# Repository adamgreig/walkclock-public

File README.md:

# walkclock

A clock that shows a map with a route that progresses day-by-day.

Display is a 64x64px LED matrix, driven by an STM32H743 on a WeAct dev board.

## Simulator

To run the simulator on a desktop:

```
cd simulator/
cargo run --release
```

The following keyboard buttons are mapped to the buttons on the hardware:

* Q/Backspace/Up: BACK
* W: QR
* E: DISPLAY
* A/Enter/Down: ENTER
* S/Left: LEFT
* D/Right: RIGHT

## Firmware

To program the firmware:

```
cd firmware/
cargo embed --release
```

Use `cargo embed --release rtt` to also attach an RTT session.

## Other Assets

* `mechanical/` contains design files for the 3d-printed holder and laser-cut
  acrylic diffuser
* `artwork/` contains the various maps and images, and a script to extract
  route pixel data from XCF files

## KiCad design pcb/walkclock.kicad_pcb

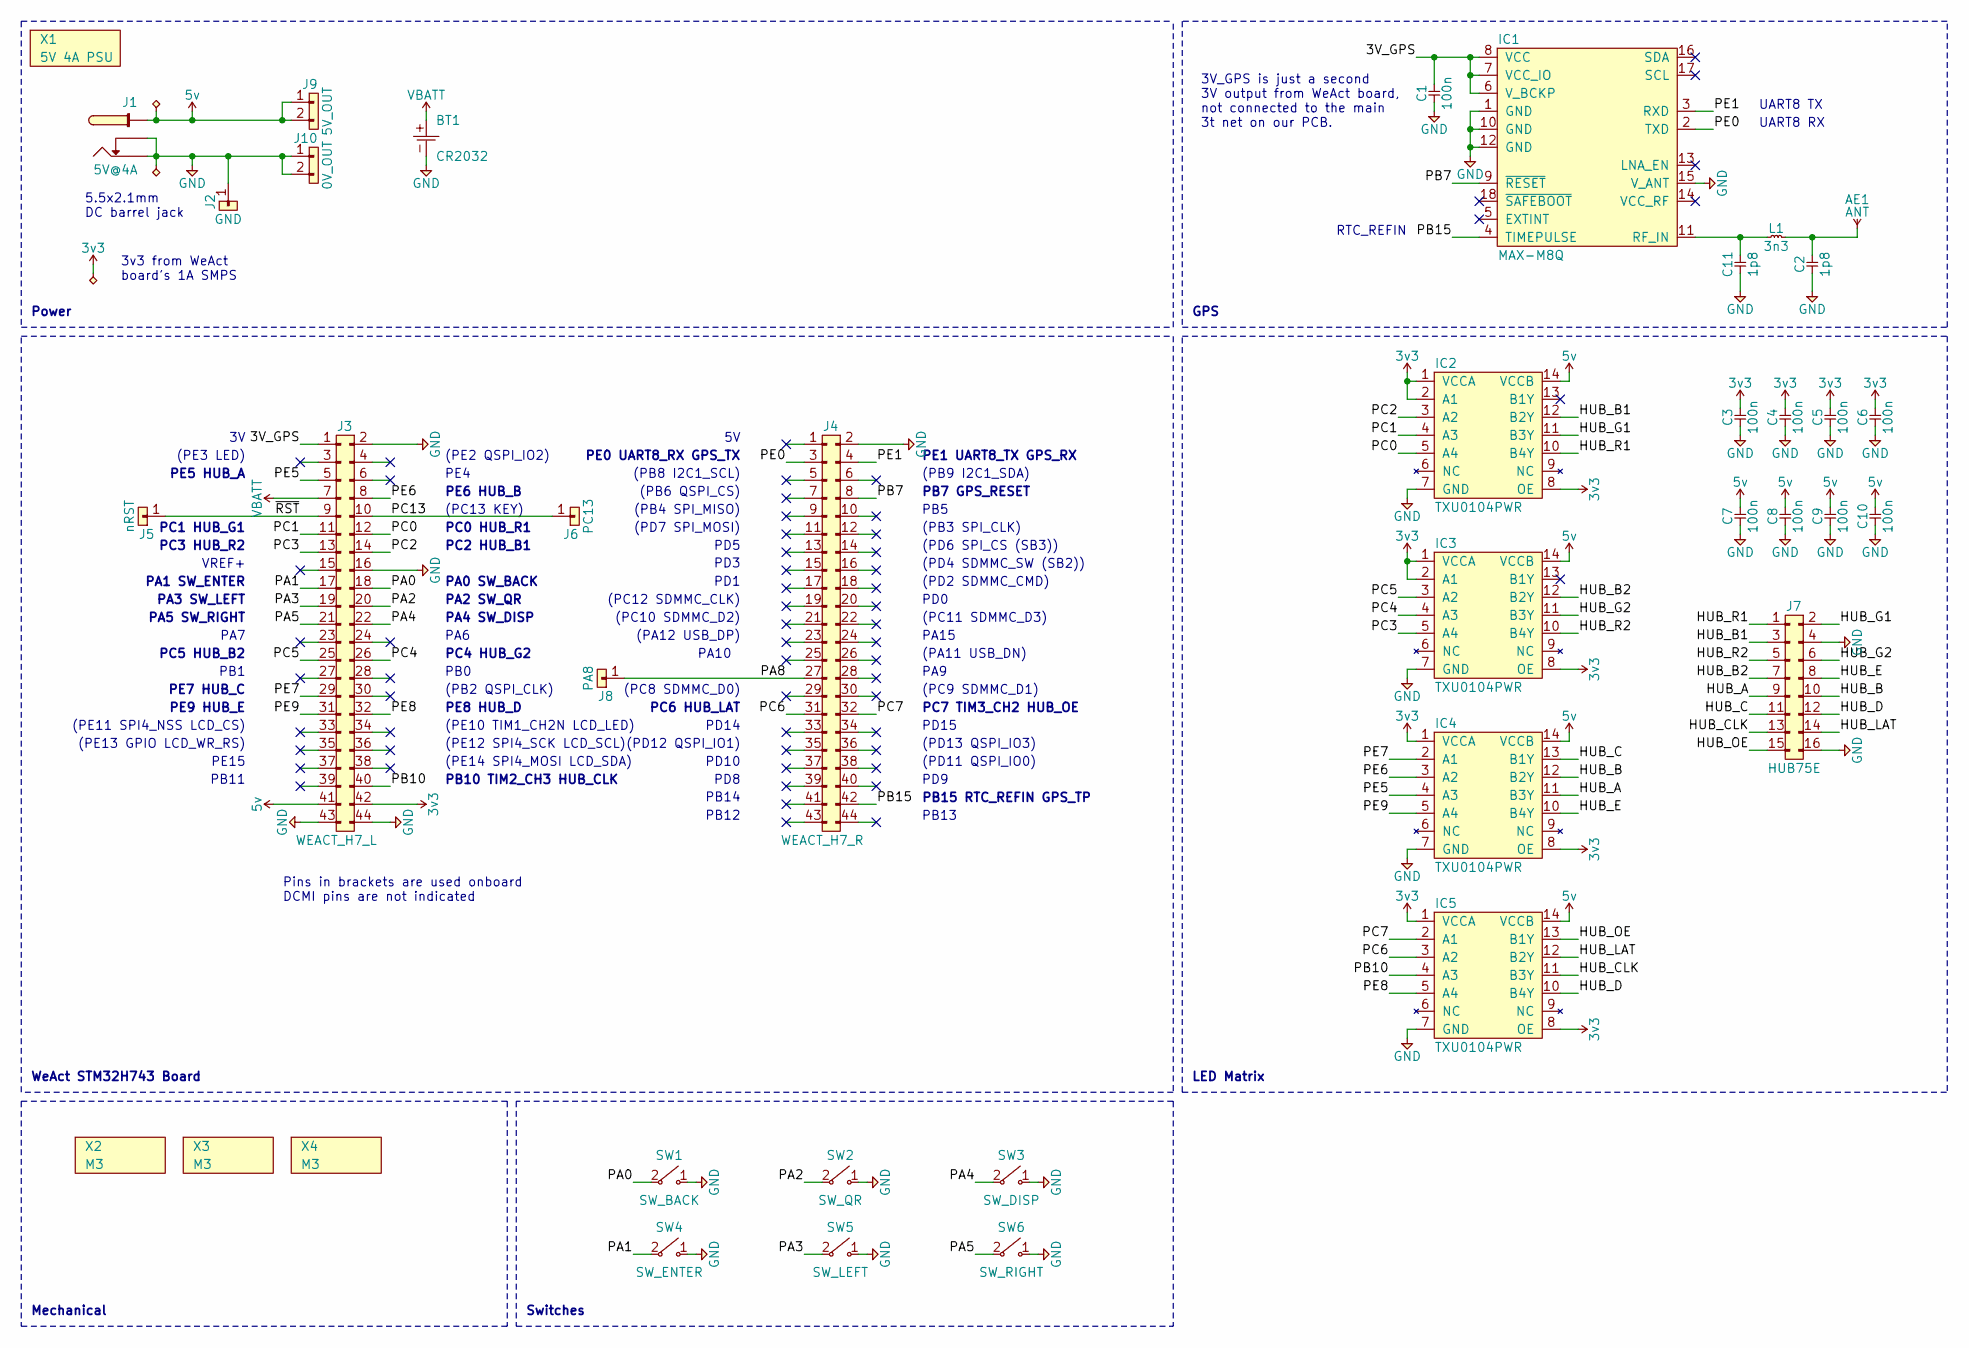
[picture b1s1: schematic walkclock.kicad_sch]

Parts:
AE1: ANT; NN01-103; Mouser 128-NN01-103
BT1: CR2032; KEYSTONE_103
C1, C3, C4, C5, C6, C7, C8, C9, C10: 100n; 0402; Mouser 963-TMK105BJ104KV8F
C2, C11: 1p8; 0402; Mouser 80-CBR04C189A5GAC
IC1: MAX-M8Q
IC2, IC3, IC4, IC5: TXU0104PWR; TSSOP-14; Mouser 595-TXU0104PWR
J1: 5V@4A; BARRELJACK
J2: GND; SIL-254P-01
J3: WEACT_H7_L; DIL-254P-44; Mouser 200-SSW12201FD
J4: WEACT_H7_R; DIL-254P-44; Mouser 200-SSW12201FD
J5: nRST; SIL-254P-01
J6: PC13; SIL-254P-01
J7: HUB75E; DIL-254P-16; Mouser 200-SSW10801FD
J8: PA8; SIL-254P-01
J9: 5V_OUT; SIL-254P-02
J10: 0V_OUT; SIL-254P-02
L1: 3n3; 0402; Mouser 81-LQW15AN3N3D10D
SW1: SW_BACK; SW_MOM_6X6; Mouser 179-TS046670BK260SMT
SW2: SW_QR; SW_MOM_6X6; Mouser 179-TS046670BK260SMT
SW3: SW_DISP; SW_MOM_6X6; Mouser 179-TS046670BK260SMT
SW4: SW_ENTER; SW_MOM_6X6; Mouser 179-TS046670BK260SMT
SW5: SW_LEFT; SW_MOM_6X6; Mouser 179-TS046670BK260SMT
SW6: SW_RIGHT; SW_MOM_6X6; Mouser 179-TS046670BK260SMT
X1: 5V 4A PSU; Mouser 418-TRE25050U11G02VI
X2, X3, X4: M3; M3_HOLE

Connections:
3v3: C3.2, C4.2, C5.2, C6.2, IC2.1 (VCCA), IC2.2 (A1), IC2.8 (OE), IC3.1 (VCCA), IC3.2 (A1), IC3.8 (OE), IC4.1 (VCCA), IC4.8 (OE), IC5.1 (VCCA), IC5.8 (OE), J3.42
5v: C7.2, C8.2, C9.2, C10.2, IC2.14 (VCCB), IC3.14 (VCCB), IC4.14 (VCCB), IC5.14 (VCCB), J1.1 (TIP), J3.41, J9.1, J9.2
/3V_GPS: C1.2, IC1.6 (V_BCKP), IC1.7 (VCC_IO), IC1.8 (VCC), J3.1
/HUB_A: IC4.11 (B3Y), J7.9
/HUB_B: IC4.12 (B2Y), J7.10
/HUB_B1: IC2.12 (B2Y), J7.3
/HUB_B2: IC3.12 (B2Y), J7.7
/HUB_C: IC4.13 (B1Y), J7.11
/HUB_CLK: IC5.11 (B3Y), J7.13
/HUB_D: IC5.10 (B4Y), J7.12
/HUB_E: IC4.10 (B4Y), J7.8
/HUB_G1: IC2.11 (B3Y), J7.2
/HUB_G2: IC3.11 (B3Y), J7.6
/HUB_LAT: IC5.12 (B2Y), J7.14
/HUB_OE: IC5.13 (B1Y), J7.15
/HUB_R1: IC2.10 (B4Y), J7.1
/HUB_R2: IC3.10 (B4Y), J7.5
/PA0: J3.18, SW1.2 ("~")
/PA1: J3.17, SW4.2 ("~")
/PA2: J3.20, SW2.2 ("~")
/PA3: J3.19, SW5.2 ("~")
/PA4: J3.22, SW3.2 ("~")
/PA5: J3.21, SW6.2 ("~")
/PA8: J4.27, J8.1
/PB7: IC1.9 (~RESET), J4.8
/PB10: IC5.4 (A3), J3.40
/PB15: IC1.4 (TIMEPULSE), J4.42
/PC0: IC2.5 (A4), J3.12
/PC1: IC2.4 (A3), J3.11
/PC2: IC2.3 (A2), J3.14
/PC3: IC3.5 (A4), J3.13
/PC4: IC3.4 (A3), J3.26
/PC5: IC3.3 (A2), J3.25
/PC6: IC5.3 (A2), J4.31
/PC7: IC5.2 (A1), J4.32
/PC13: J3.10, J6.1
/PE0: IC1.2 (TXD), J4.3
/PE1: IC1.3 (RXD), J4.4
/PE5: IC4.4 (A3), J3.5
/PE6: IC4.3 (A2), J3.8
/PE7: IC4.2 (A1), J3.29
/PE8: IC5.5 (A4), J3.32
/PE9: IC4.5 (A4), J3.31
/~RST: J3.9, J5.1
GND: BT1.-, C1.1, C2.1, C3.1, C4.1, C5.1, C6.1, C7.1, C8.1, C9.1, C10.1, C11.1, IC1.1 (GND), IC1.10 (GND), IC1.12 (GND), IC1.15 (V_ANT), IC2.7 (GND), IC3.7 (GND), IC4.7 (GND), IC5.7 (GND), J1.2 (SW), J1.3 (RING), J2.1, J3.2, J3.16, J3.43, J3.44, J4.2, J7.4, J7.16, J10.1, J10.2, SW1.1 ("~"), SW2.1 ("~"), SW3.1 ("~"), SW4.1 ("~"), SW5.1 ("~"), SW6.1 ("~")
unnamed: AE1.1, C2.2, L1.2
unnamed: C11.2, IC1.11 (RF_IN), L1.1
VBATT: BT1.+, J3.7

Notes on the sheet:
(PE11 SPI4_NSS LCD_CS)
(PA11 USB_DN)
PD14
PC1 HUB_G1
5.5x2.1mm DC barrel jack
PD15
Mechanical
PC2 HUB_B1
GPS
(PE13 GPIO LCD_WR_RS)
PE8 HUB_D
UART8 RX
(PB2 QSPI_CLK)
PA7
(PC8 SDMMC_D0)
PA3 SW_LEFT
(PC12 SDMMC_CLK)
(PE10 TIM1_CH2N LCD_LED)
Switches
(PC9 SDMMC_D1)
(PC11 SDMMC_D3)
(PD12 QSPI_IO1)
PC3 HUB_R2
PD9
(PD6 SPI_CS (SB3))
UART8 TX
(PD4 SDMMC_SW (SB2))
(PB6 QSPI_CS)
3v3 from WeAct board's 1A SMPS
(PE12 SPI4_SCK LCD_SCL)
PE0 UART8_RX GPS_TX
PD8
PA15
PB1
(PE2 QSPI_IO2)
PE1 UART8_TX GPS_RX
PE5 HUB_A
PE6 HUB_B
PC4 HUB_G2
PB14

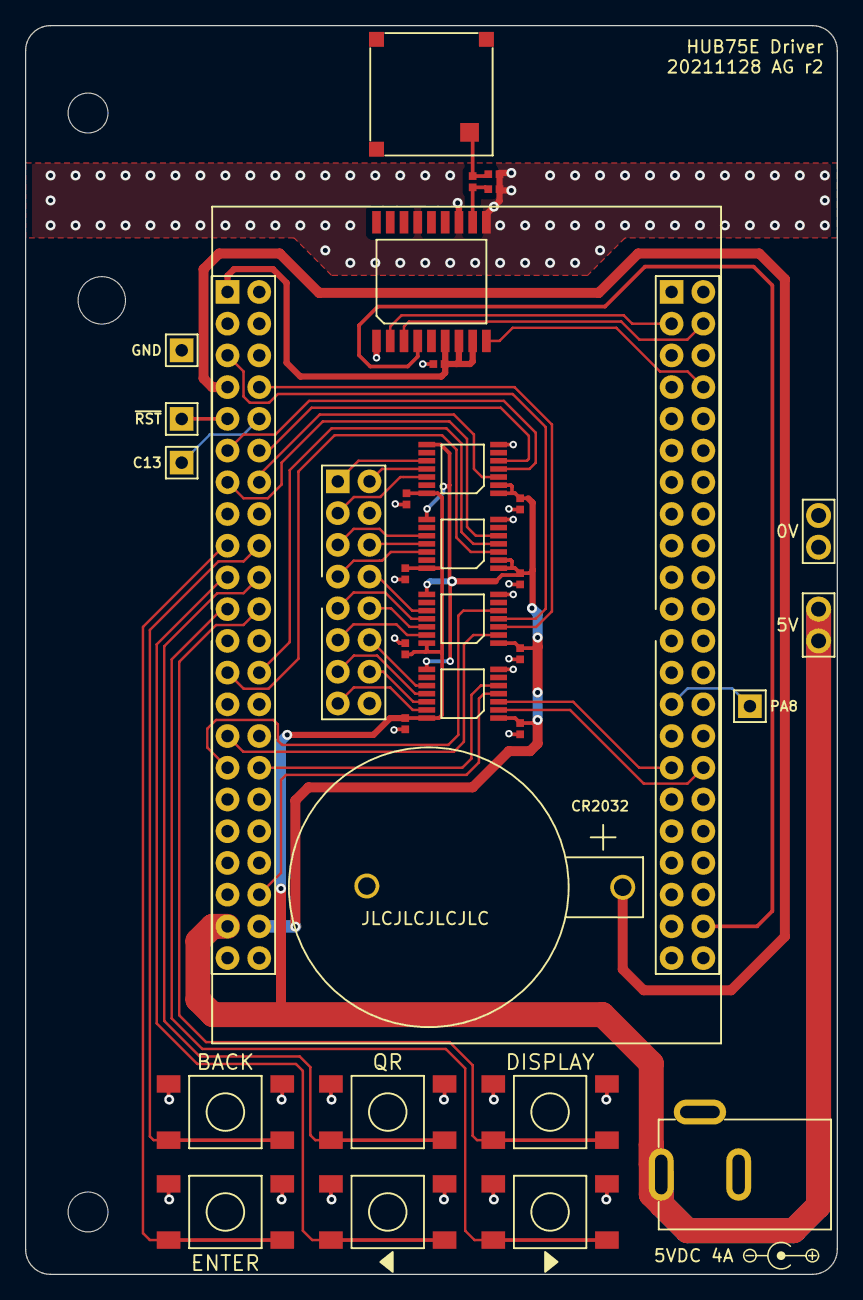
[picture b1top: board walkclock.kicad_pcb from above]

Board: 2 copper layers, 65.0 x 100.0 mm, 38 parts (0 on the bottom side), 48 nets.

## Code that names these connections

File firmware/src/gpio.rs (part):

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
pub fn setup(gpioa: Gpio, gpiob: Gpio, gpioc: Gpio, _gpiod: Gpio, gpioe: Gpio) -> Pins {
    // GPIOA
    // PA0: Input pulled up, SW_BACK
    // PA1: Input pulled up, SW_ENTER
    // PA2: Input pulled up, SW_QR
    // PA3: Input pulled up, SW_LEFT
    // PA4: Input pulled up, SW_DISP
    // PA5: Input pulled up, SW_RIGHT
    // PA6-7: Unused
    // PA8: AF0, MCO1 for LSE calibration
    // PA9-12: Unused
    // PA13: AF0 SWDIO pulled up
    // PA14: AF0 SWCLK pulled down
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
    // GPIOB
    // PB0-PB6: Unused
    // PB7: Output, GPS_RESET
    // PB8-9: Unused
    // PB10: AF1, TIM2_CH3, HUB_CLK
    // PB11-14: Unused
    // PB15: AF0, RTC_REFIN
    write_reg!(gpio, gpiob, ODR, 0);
    write_reg!(gpio, gpiob, MODER, MODER7: Output, MODER10: Alternate, MODER15: Alternate);
    write_reg!(gpio, gpiob, OSPEEDR, OSPEEDR10: MediumSpeed);
    write_reg!(gpio, gpiob, AFRH, AFR10: 1, AFR15: 0);

    // GPIOC
    // PC0: Output, HUB_R1
    // PC1: Output, HUB_G1
    // PC2: Output, HUB_B1
    // PC3: Output, HUB_R2
    // PC4: Output, HUB_G2
    // PC5: Output, HUB_B2
    // PC6: Output, HUB_LAT
    // PC7: AF2, TIM3_CH2, HUB_OE
    // PC8-PC12: Unused
    // PC13: Input, KEY / RTC_CALIB
    // PC14-PC15: Unused
    // HUB pins need to be medium speed <=60MHz.
    write_reg!(gpio, gpioc, ODR, 0);
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    // PD0-15: Unused

    // GPIOE
    // PE0: AF8, UART8_RX, GPS_TX
    // PE1: AF8, UART8_TX, GPS_RX
    // PE2: Unused
    // PE3: Output, LED
    // PE4: Unused
    // PE5: Output, HUB_A
    // PE6: Output, HUB_B
    // PE7: Output, HUB_C
    // PE8: Output, HUB_D
    // PE9: Output, HUB_E
    // PE10: AF1, TIM1_CH2N, LCD_LED
    // PE11: AF5, SPI4_NSS, LCD_CS
    // PE12: AF5, SPI4_SCK, LCD_SCL
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    }
}

/// Force PB15 to AF0, used for RTC REF_IN from the GPS.
pub fn pb15_rtc() {
    // NOTE(unsafe): No other code accesses this register outside of the initialisation
    // NOTE(unsafe): routine above and `pb15_tim()` below, which changes the same field.
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    }
}

/// Force PB15 to AF2, used for TIM12 CH2 input for calibration measurement.
pub fn pb15_tim() {
    // NOTE(unsafe): No other code accesses this register outside of the initialisation
    // NOTE(unsafe): routine above and `pb15_rtc()` above, which changes the same field.
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
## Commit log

2021-12-31 Initial commit: public export of walkclock repo
2021-12-31 Add image of walkclock to README
